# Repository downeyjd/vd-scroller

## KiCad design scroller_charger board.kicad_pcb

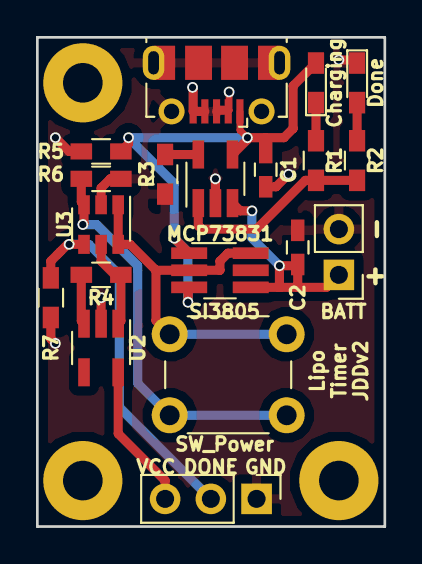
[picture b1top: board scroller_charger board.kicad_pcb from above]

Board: 2 copper layers, 19.3 x 27.2 mm, 19 parts (0 on the bottom side), 13 nets.

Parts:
BATT: JST_2PIN; Pin_Header_Straight_1x02_Pitch2.54mm
C1, C2: 1uF; C_0603_HandSoldering
Charging: RED; LED_0603_HandSoldering
Done: GREEN; LED_0603_HandSoldering
J1: USB_OTG; USB_Micro-B_Molex-105017-0001
J4: Conn_01x03; Pin_Header_Straight_1x03_Pitch2.54mm
MCP73831: MCP73831_SOT23-5; SOT-23-5_HandSoldering
R1, R2: 470; R_0603_HandSoldering
R3: 2k; R_0603_HandSoldering
R4, R7: 10k; R_0603_HandSoldering
R5: 100k; R_0603_HandSoldering
R6: 43k; R_0603_HandSoldering
SI3805: SI3805; TSOT-23-6_HandSoldering
SW_Power: SW_Power; SW_PUSH_6mm_h13mm
U2: AP2112K-3.3; SOT-23-5_HandSoldering
U3: TPL5111; SOT-23-6

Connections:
/DONE: J4.2, R7.2, U3.4
GND: BATT.2, C1.1, C2.2, Done.1, J1.2, J1.3, J1.4, J1.5, J1.6, J4.1, MCP73831.2, R3.1, R5.2, R6.1, R7.1, U2.2, U3.2
unnamed: BATT.1, C2.1, MCP73831.3, SI3805.4
unnamed: Charging.1, R1.2
unnamed: Done.2, R2.2
unnamed: MCP73831.1, R1.1, R2.1
unnamed: MCP73831.5, R3.2
unnamed: R4.1, U2.3
unnamed: R4.2, U2.1, U3.5
unnamed: R6.2, SW_Power.2, U3.3
unnamed: SI3805.2, SI3805.6, SW_Power.1, U3.1, U3.6
VBUS: C1.2, Charging.2, J1.1, MCP73831.4, R5.1, SI3805.1, SI3805.3
VCC: J4.3, U2.5

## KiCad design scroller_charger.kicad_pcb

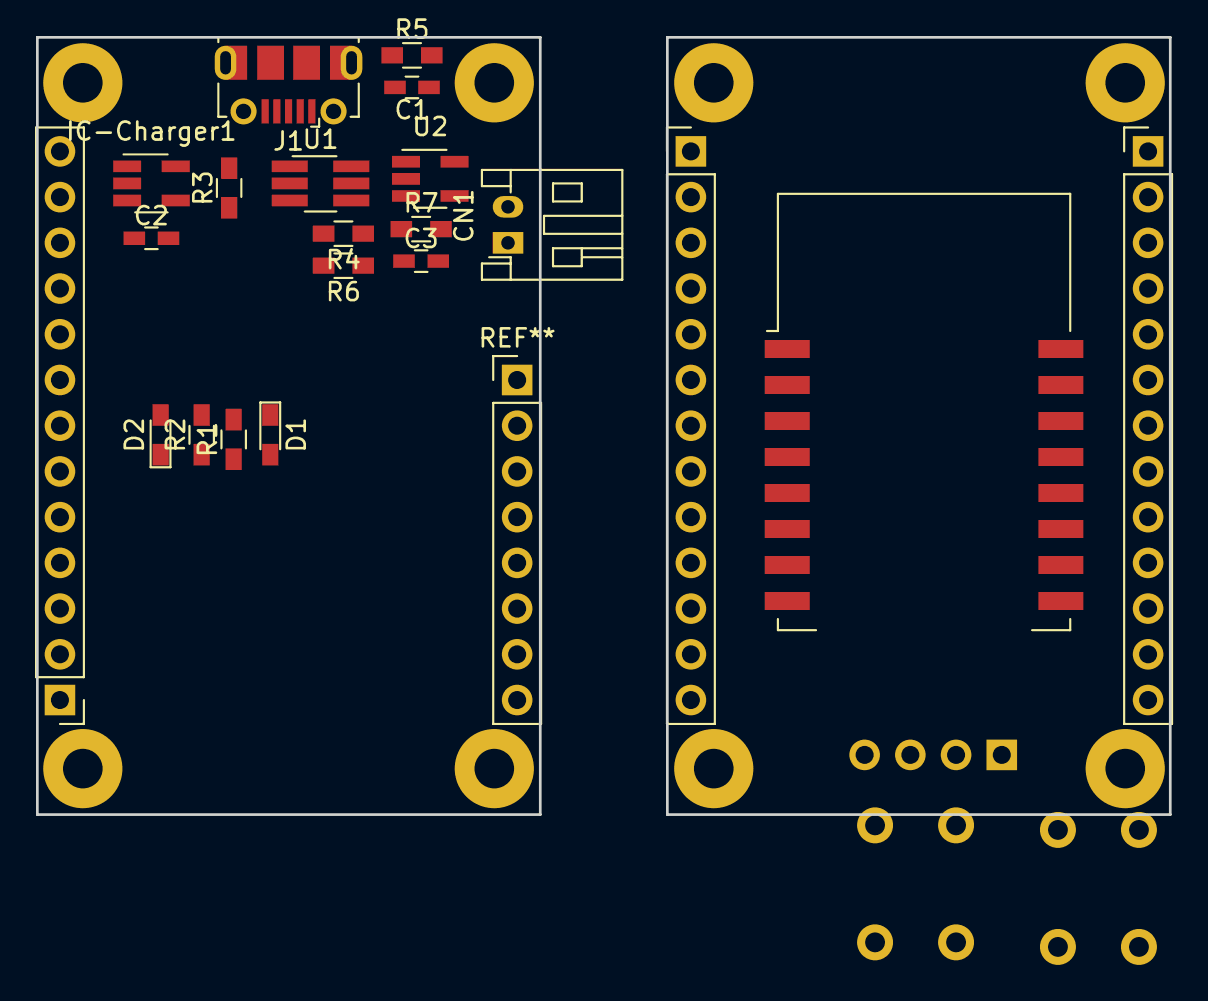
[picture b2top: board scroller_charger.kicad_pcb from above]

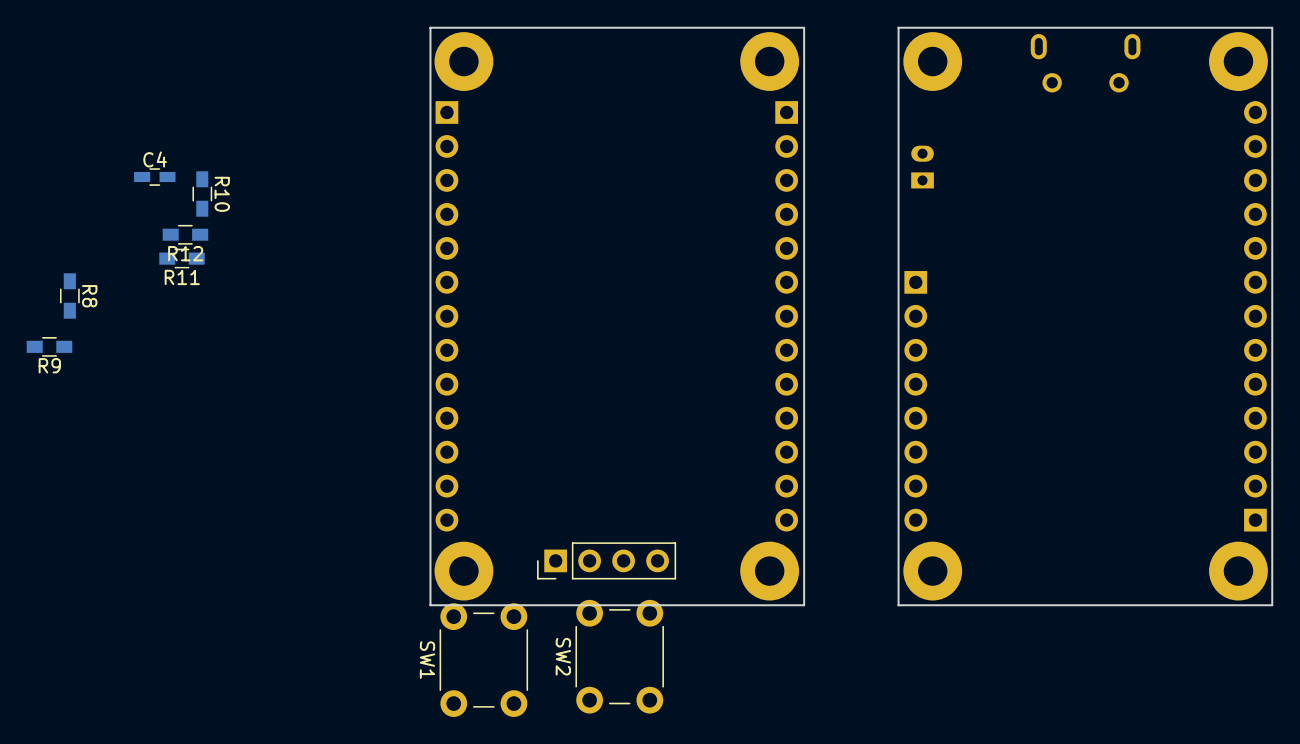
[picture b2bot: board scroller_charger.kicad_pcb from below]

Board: 2 copper layers, 62.9 x 43.2 mm, 28 parts (9 on the bottom side), 18 nets, no tracks yet.

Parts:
C1, C2, C3, C4: 1uF; C_0603_HandSoldering
CN1: JST_2PIN; JST_PH_S2B-PH-K_02x2.00mm_Angled
D1: RED; LED_0603_HandSoldering
D2: GREEN; LED_0603_HandSoldering
IC-Charger1: MCP73831_SOT23-5; SOT-23-5_HandSoldering
J1: USB_OTG; USB_Micro-B_Molex-105017-0001
J2: Conn_01x08; Pin_Header_Straight_1x13_Pitch2.54mm
J4: Conn_01x04; Pin_Header_Straight_1x04_Pitch2.54mm
R1, R2: 470; R_0603_HandSoldering
R3: 2k; R_0603_HandSoldering
R4, R6, R8, R9, R10, R11, R12: 10k; R_0603_HandSoldering
R5: 100k; R_0603_HandSoldering
R7: 2.2k; R_0603_HandSoldering
SW1: SW_Reset; SW_PUSH_6mm_h13mm
SW2: SW_Flash; SW_PUSH_6mm_h13mm
U1: SI3805; TSOT-23-6_HandSoldering
U2: AP2112K-3.3; SOT-23-5_HandSoldering
X1: ESP-12; ESP-12E

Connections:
/ADC: R6.2, R7.1, X1.2
/Rx: J4.2, X1.15
/Tx: J4.3, X1.16
GND: C1.1, C2.2, C3.2, C4.2, CN1.2, D2.1, IC-Charger1.2, J1.5, J4.1, R3.1, R5.2, R7.2, R10.1, SW1.2, SW2.2, U2.2, X1.9
unnamed: C2.1, CN1.1, IC-Charger1.3, U1.4
unnamed: C3.1, R4.2, R6.1, U1.2, U1.6, U2.1
unnamed: D1.1, R1.2
unnamed: D2.2, R2.2
unnamed: IC-Charger1.1, R1.1, R2.1
unnamed: IC-Charger1.5, R3.2
unnamed: R4.1, U2.3
unnamed: R8.2, SW1.1, X1.1
unnamed: R9.2, X1.3
unnamed: R10.2, X1.10
unnamed: R11.1, SW2.1, X1.12
unnamed: R12.1, X1.11
VBUS: C1.2, D1.2, IC-Charger1.4, J1.1, R5.1, U1.1, U1.3
VCC: C4.1, J4.4, R8.1, R9.1, R11.2, R12.2, U2.5, X1.8

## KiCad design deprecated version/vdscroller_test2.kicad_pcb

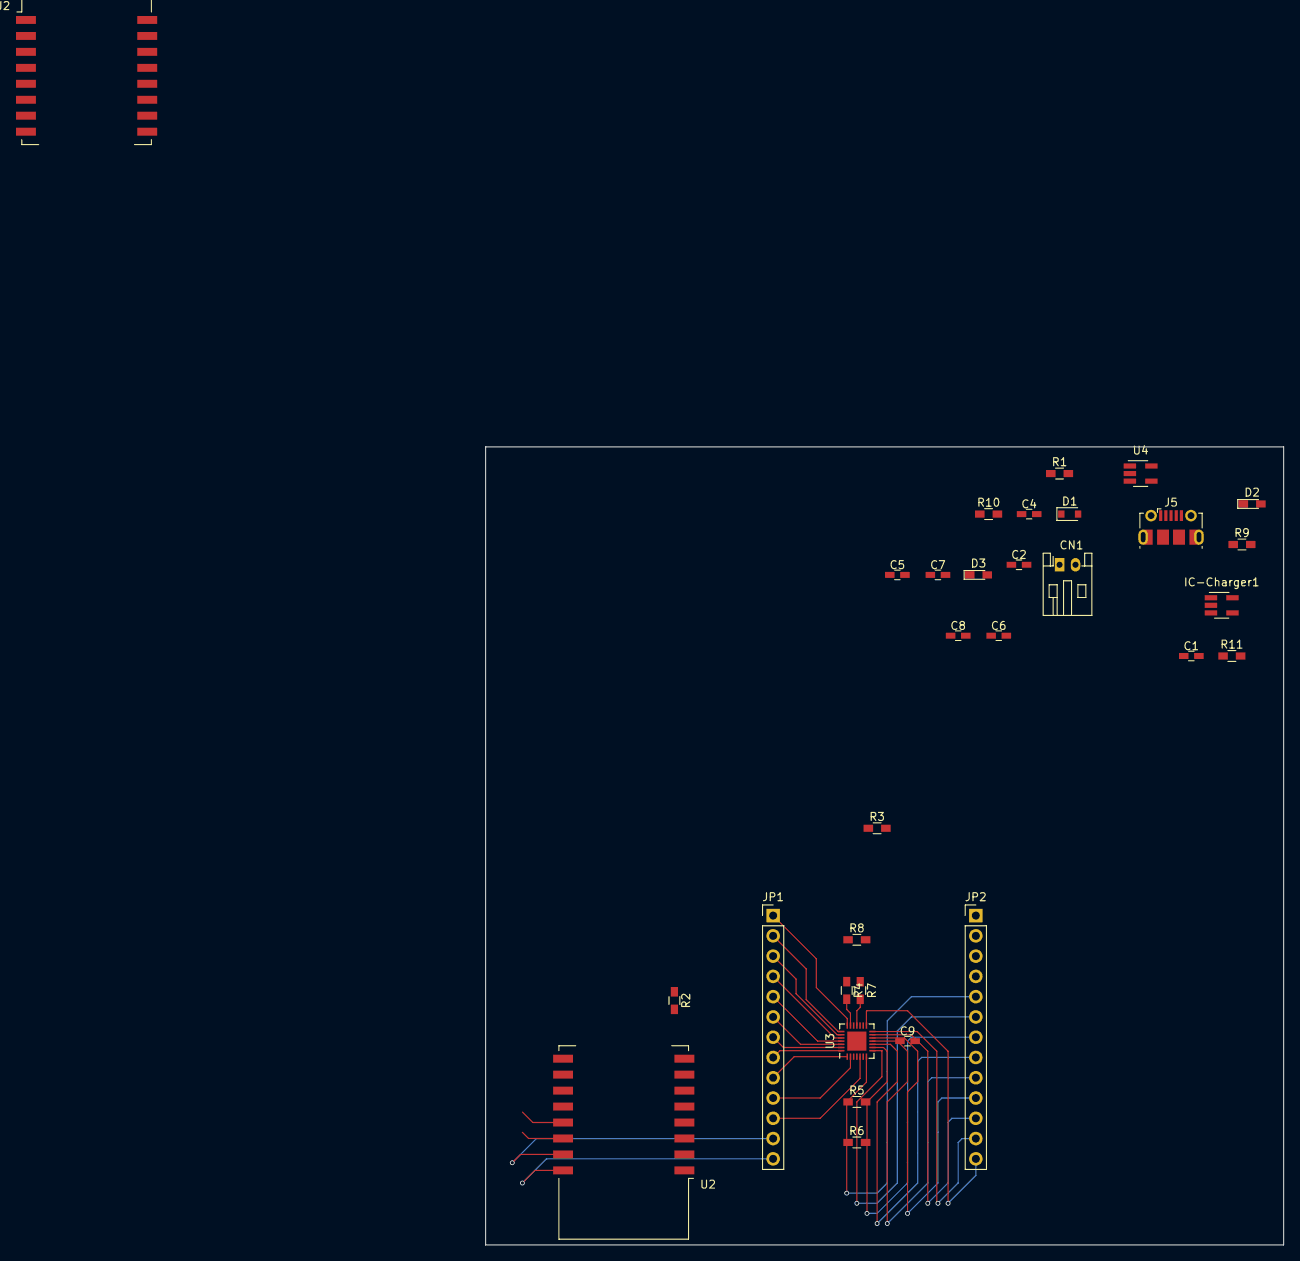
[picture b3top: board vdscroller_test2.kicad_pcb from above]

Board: 2 copper layers, 100.0 x 100.0 mm, 31 parts (0 on the bottom side), 38 nets.

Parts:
C1, C2, C4, C5, C6, C7: 10uF; C_0603_HandSoldering
C8, C9: 0.1uF; C_0603_HandSoldering
CN1: JST_2PIN; JST_PH_S2B-PH-K_02x2.00mm_Angled
D1: 20V1A; D_0805
D2: RED; LED_0603_HandSoldering
D3: GREEN; LED_0603_HandSoldering
IC-Charger1: MCP73831_SOT23-5; SOT-23-5_HandSoldering
J5: USB_OTG; USB_Micro-B_Molex-105017-0001
JP1, JP2: PINHD-1X13; Pin_Header_Straight_1x13_Pitch2.54mm
R1, R2, R11: 10k; R_0603_HandSoldering
R3, R4, R5, R6, R7, R8: 20k; R_0603_HandSoldering
R9, R10: 470; R_0603_HandSoldering
U2, U2#2: ESP-12; ESP-12E
U3: IS31FL3731; QFN-28-1EP_4x4mm_Pitch0.4mm
U4: AP2112K-3.3; SOT-23-5_HandSoldering

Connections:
/ADDR: R7.2, U3.18
/CA1: JP1.1, U3.21
/CA2: JP1.2, U3.22
/CA3: JP1.3, U3.23
/CA4: JP1.4, U3.24
/CA5: JP1.5, U3.25
/CA6: JP1.6, U3.26
/CA7: JP1.7, U3.27
/CA8: JP1.8, U3.28
/CA9: JP1.9, U3.1
/CB1: JP2.5, U3.7
/CB2: JP2.6, U3.8
/CB3: JP2.7, U3.9
/CB4: JP2.8, U3.10
/CB5: JP2.9, U3.11
/CB6: JP2.10, U3.12
/CB7: JP2.11, U3.13
/CB8: JP2.12, U3.14
/CB9: JP2.13, U3.15
/CFILT: C9.1, U3.16
/INTB: R5.2, U3.4
/REXT: R8.2, U3.6
/Rx: JP1.12, U2.15
/SCL: R4.2, U2.13, U3.20
/SDA: R3.2, U2.14, U3.19
/SDB: R6.2, U3.3
/Tx: JP1.13, U2.16
GND: C1.1, C2.2, C4.2, C5.1, C6.2, C7.2, C8.2, C9.2, CN1.1, D3.1, IC-Charger1.2, J5.5, JP1.11, R7.1, R8.1, R11.1, U2.9, U3.5, U4.2
unnamed: C1.2, D2.2, IC-Charger1.4, J5.1
unnamed: C2.1, CN1.2, D1.2, IC-Charger1.3
unnamed: C4.1, D1.1, R1.2, U4.1
unnamed: D2.1, R9.2
unnamed: D3.2, R10.2
unnamed: IC-Charger1.1, R9.1, R10.1
unnamed: IC-Charger1.5, R11.2
unnamed: R1.1, U4.3
unnamed: R2.2, U2.3
VCC: C5.2, C6.1, C7.1, C8.1, JP1.10, R2.1, R3.1, R4.1, R5.1, R6.1, U2.8, U3.2, U4.5

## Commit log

2018-06-26 Test
    Test
2018-06-26 Upgrade to ESP32
    Moving from ESP8266 to ESP32 Feather from Adafruit
2018-06-26 Porting to ESP32/NoBatt
    Removed Battery/Sleep code, moved from ESP8266 to ESP32, single SSID, no RTC mem, display not working - unsure whether that's software or hardware
